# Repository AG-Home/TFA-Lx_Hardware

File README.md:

# TFA-Lx_Hardware
Hardware Design for TFA project

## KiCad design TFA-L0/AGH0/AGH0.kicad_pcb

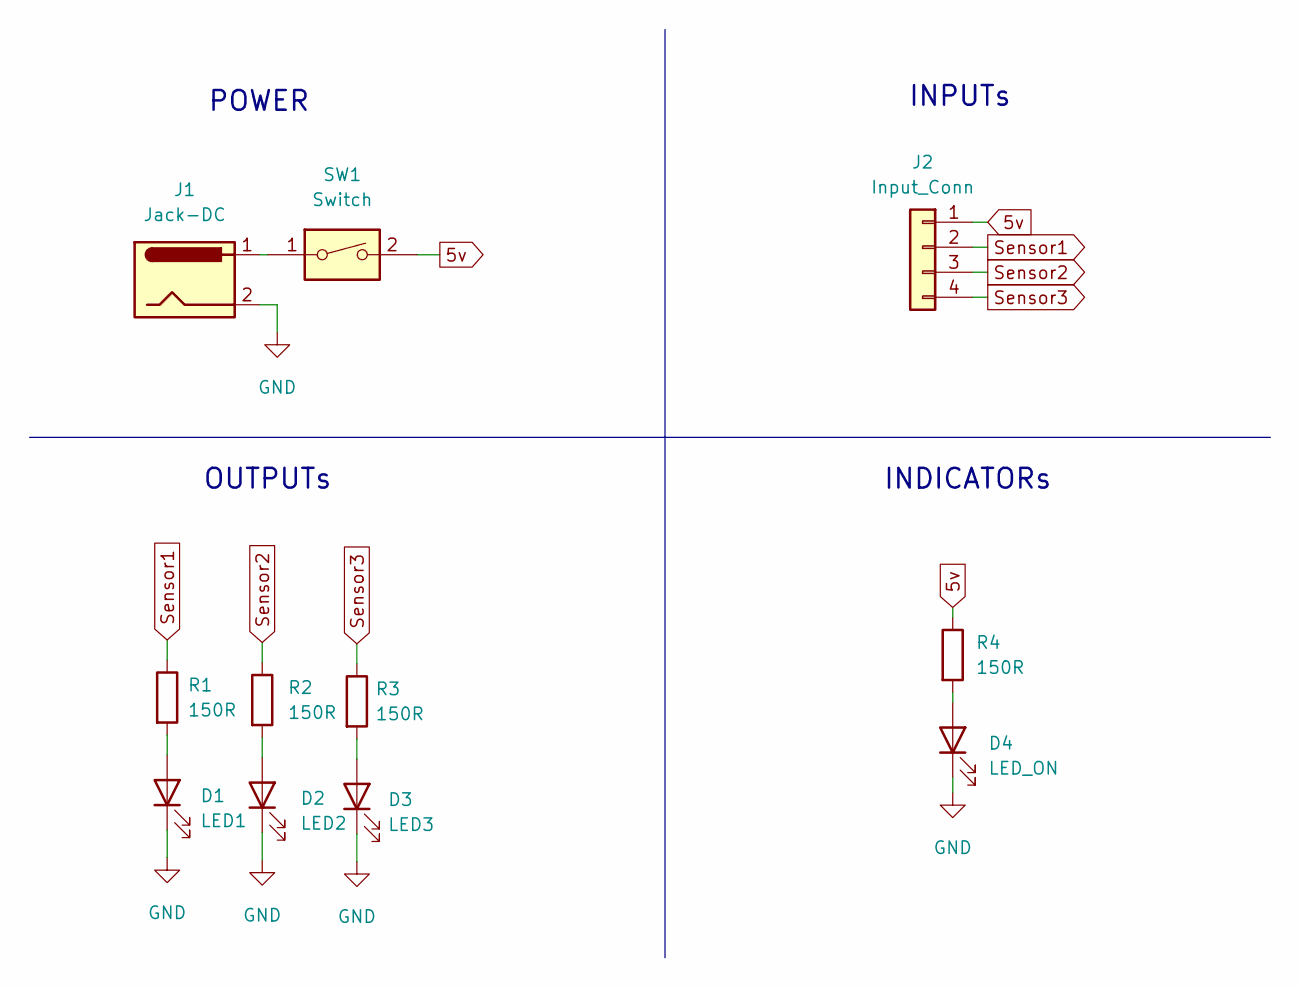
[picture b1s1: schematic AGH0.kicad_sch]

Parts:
D1: LED1; LED_D5.0mm
D2: LED2; LED_D5.0mm
D3: LED3; LED_D5.0mm
D4: LED_ON; LED_D5.0mm
J1: Jack-DC; BarrelJack_Horizontal
J2: Input_Conn; TerminalBlock_4Ucon_1x04_P3.50mm_Horizontal
R1, R2, R3, R4: 150R; R_Axial_DIN0204_L3.6mm_D1.6mm_P7.62mm_Horizontal
SW1: Switch; TerminalBlock_4Ucon_1x02_P3.50mm_Horizontal

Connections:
5v: J2.1, R4.1, SW1.2
GND: D1.1 (K), D2.1 (K), D3.1 (K), D4.1 (K), J1.2
unnamed: D1.2 (A), R1.2
unnamed: D2.2 (A), R2.2
unnamed: D3.2 (A), R3.2
unnamed: D4.2 (A), R4.2
unnamed: J1.1, SW1.1
Sensor1: J2.2, R1.1
Sensor2: J2.3, R2.1
Sensor3: J2.4, R3.1

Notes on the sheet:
POWER
OUTPUTs
INPUTs
INDICATORs

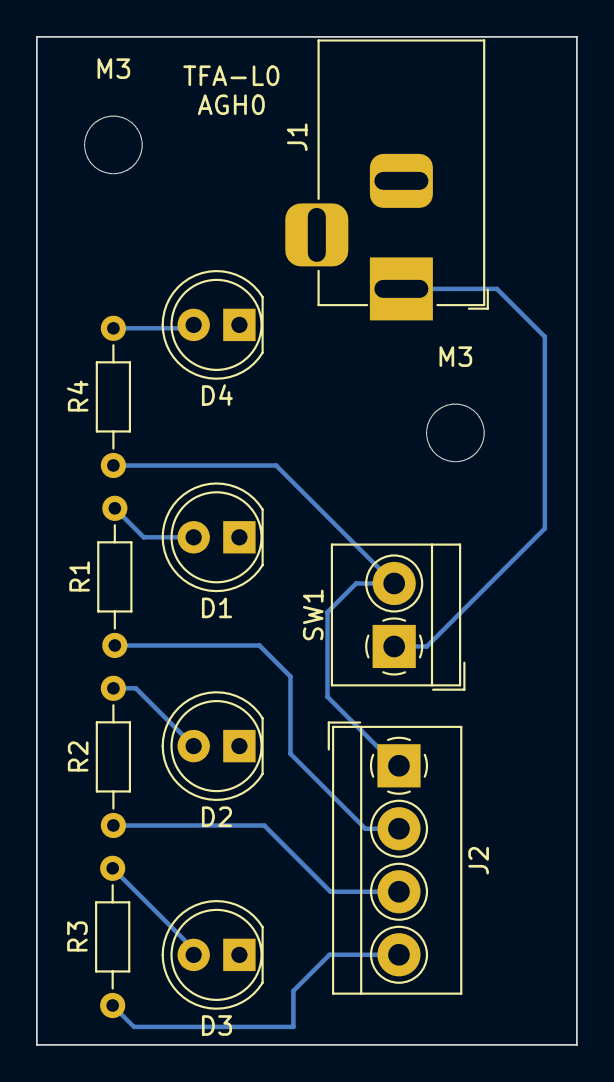
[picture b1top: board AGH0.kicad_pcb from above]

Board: 2 copper layers, 30.0 x 56.0 mm, 13 parts (0 on the bottom side), 10 nets.

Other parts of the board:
M3, M3#2: 3.2mm; MountingHole_3.2mm_M3

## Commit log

2024-04-05 feat: Create kicad project
2024-04-06 feat: Add regulator
2024-04-16 feat: Add output component
2024-04-30 feat: Add microcontroller
2024-12-18 Add TFA-L0 project
